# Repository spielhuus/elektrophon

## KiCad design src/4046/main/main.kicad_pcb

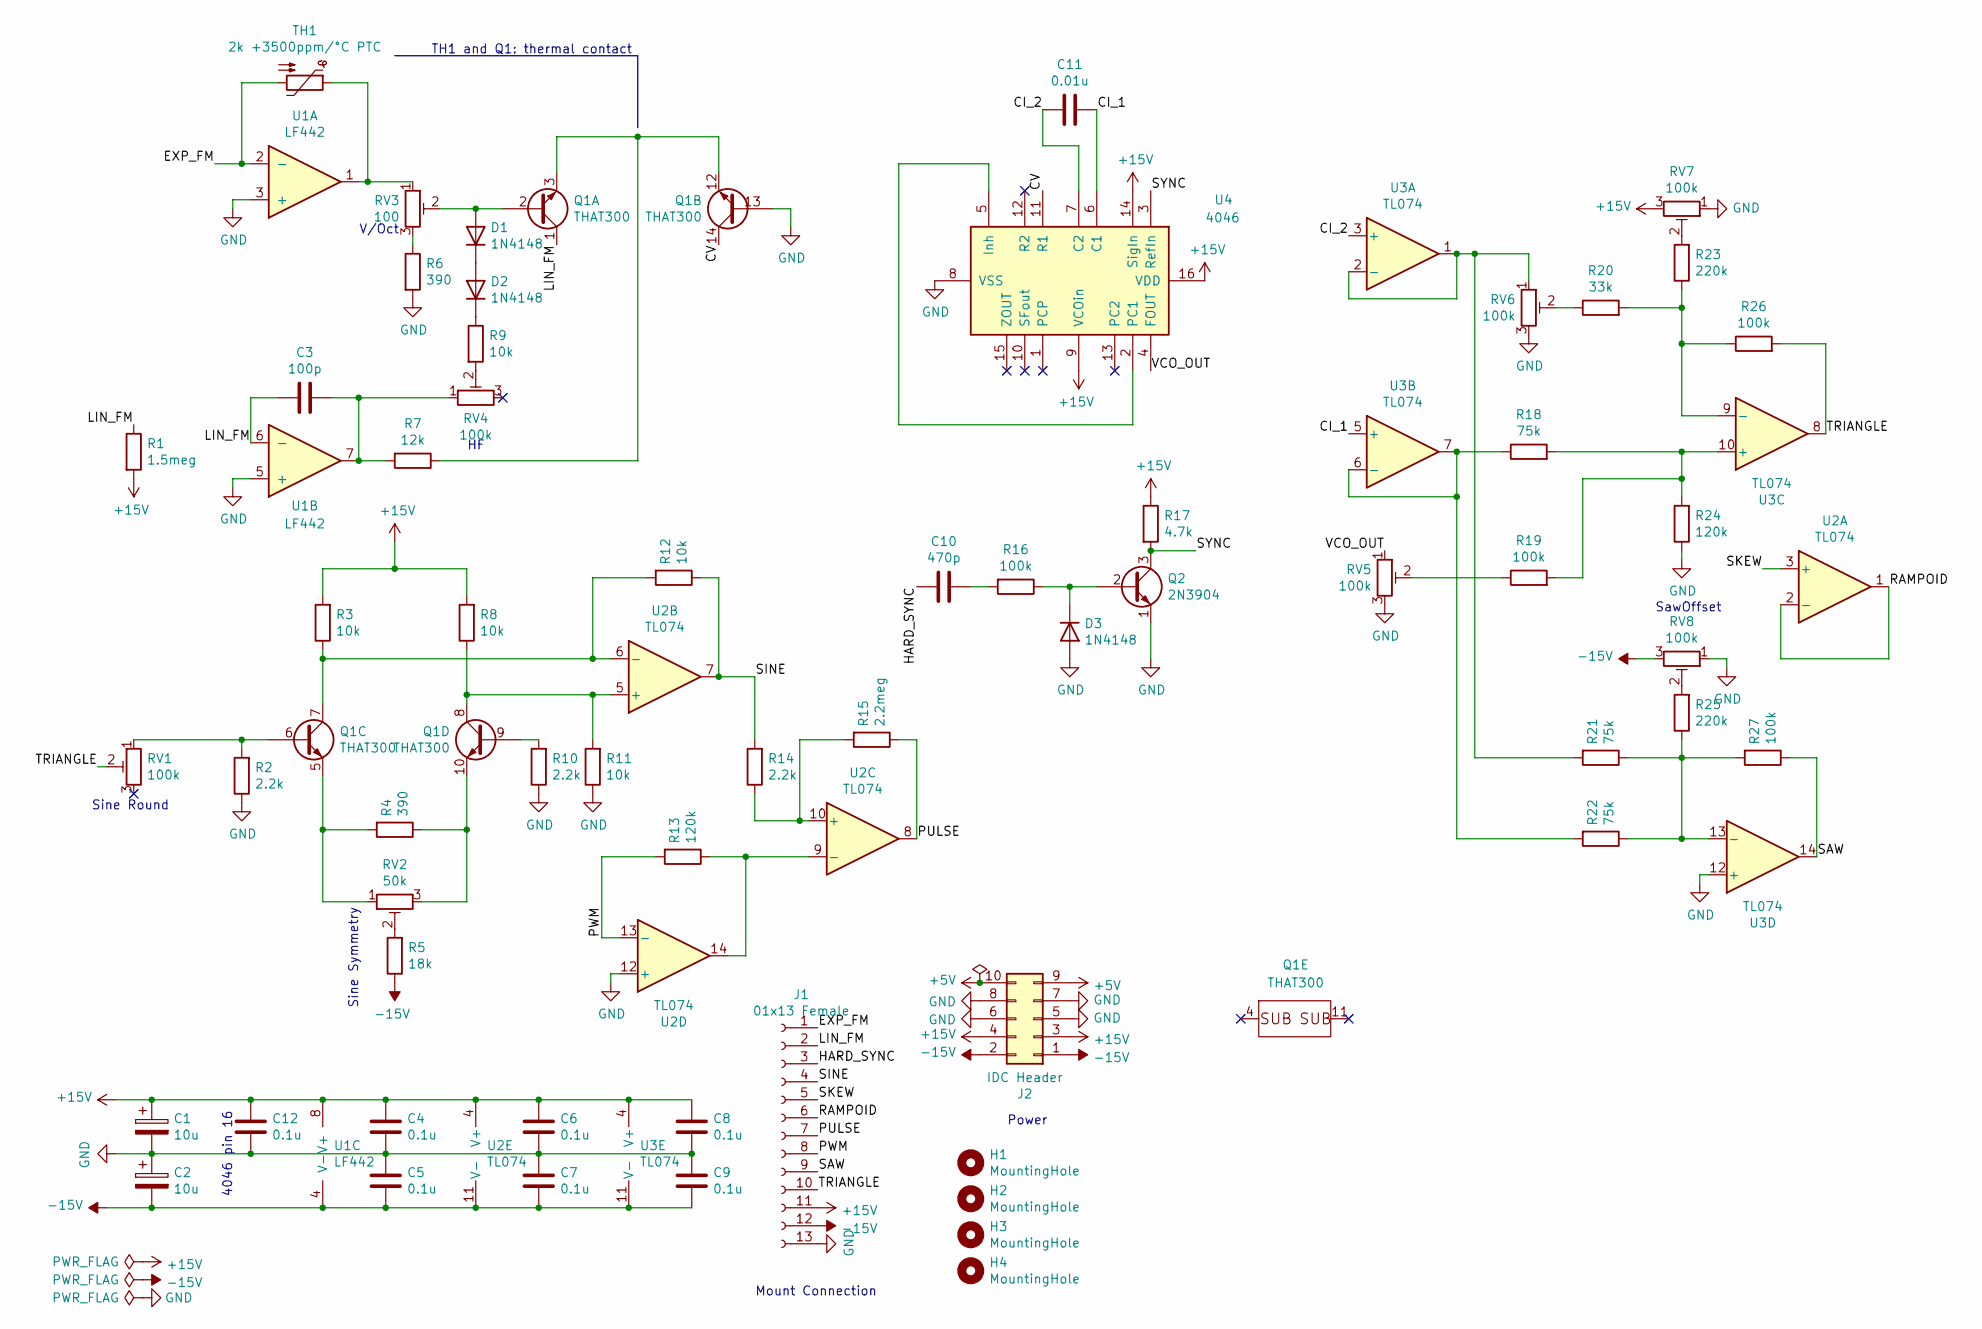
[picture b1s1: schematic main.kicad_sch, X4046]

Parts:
C1, C2: 10u; CP_Radial_D5.0mm_P2.50mm
C3: 100p; C_Disc_D3.4mm_W2.1mm_P2.50mm
C4, C5, C6, C7, C8, C9, C12: 0.1u; C_Disc_D3.4mm_W2.1mm_P2.50mm
C10: 470p; C_Disc_D3.4mm_W2.1mm_P2.50mm
C11: 0.01u; C_Rect_L4.6mm_W3.0mm_P2.50mm_MKS02_FKP02
D1, D2, D3: 1N4148; D_DO-35_SOD27_P7.62mm_Horizontal
H1, H2, H3, H4: MountingHole; MountingHole_2.2mm_M2
J1: 01x13 Female; PinSocket_1x13_P2.54mm_Vertical
J2: IDC Header; IDC-Header_2x05_P2.54mm_Vertical
Q1: THAT300; DIP-14_W7.62mm_Socket
Q2: 2N3904; TO-92_Inline_Wide
R1: 1.5meg; R_Axial_DIN0207_L6.3mm_D2.5mm_P10.16mm_Horizontal
R2, R10, R14: 2.2k; R_Axial_DIN0207_L6.3mm_D2.5mm_P10.16mm_Horizontal
R3, R8, R9, R11: 10k; R_Axial_DIN0207_L6.3mm_D2.5mm_P10.16mm_Horizontal
R4, R6: 390; R_Axial_DIN0207_L6.3mm_D2.5mm_P10.16mm_Horizontal
R5: 18k; R_Axial_DIN0207_L6.3mm_D2.5mm_P10.16mm_Horizontal
R7: 12k; R_Axial_DIN0207_L6.3mm_D2.5mm_P10.16mm_Horizontal
R12: 10k; R_Axial_DIN0207_L6.3mm_D2.5mm_P2.54mm_Vertical
R13: 120k; R_Axial_DIN0207_L6.3mm_D2.5mm_P2.54mm_Vertical
R15: 2.2meg; R_Axial_DIN0207_L6.3mm_D2.5mm_P2.54mm_Vertical
R16, R19: 100k; R_Axial_DIN0207_L6.3mm_D2.5mm_P10.16mm_Horizontal
R17: 4.7k; R_Axial_DIN0207_L6.3mm_D2.5mm_P10.16mm_Horizontal
R18, R21, R22: 75k; R_Axial_DIN0207_L6.3mm_D2.5mm_P10.16mm_Horizontal
R20: 33k; R_Axial_DIN0207_L6.3mm_D2.5mm_P10.16mm_Horizontal
R23, R25: 220k; R_Axial_DIN0207_L6.3mm_D2.5mm_P10.16mm_Horizontal
R24: 120k; R_Axial_DIN0207_L6.3mm_D2.5mm_P10.16mm_Horizontal
R26, R27: 100k; R_Axial_DIN0207_L6.3mm_D2.5mm_P2.54mm_Vertical
RV1, RV4, RV5, RV6, RV7, RV8: 100k; Potentiometer_Bourns_3296Z_Horizontal
RV2: 50k; Potentiometer_Bourns_3296Z_Horizontal
RV3: 100; Potentiometer_Bourns_3296Z_Horizontal
TH1: 2k +3500ppm/°C PTC; R_Axial_DIN0204_L3.6mm_D1.6mm_P2.54mm_Vertical
U1: LF442; DIP-8_W7.62mm_Socket
U2, U3: TL074; DIP-14_W7.62mm_Socket
U4: 4046; DIP-16_W7.62mm_Socket

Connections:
+5V: J2.9, J2.10
+15V: C1.1, C4.1, C6.1, C8.1, C12.1, J1.11, J2.3, J2.4, R1.2, R3.2, R8.2, R17.1, RV7.3, U1.8 (V+), U2.4 (V+), U3.4 (V+), U4.9 (VCOin), U4.14 (SigIn), U4.16 (VDD)
-15V: C2.2, C5.2, C7.2, C9.2, J1.12, J2.1, J2.2, R5.1, RV8.3, U1.4 (V-), U2.11 (V-), U3.11 (V-)
/CI_1: C11.2, U3.5 (+), U4.6 (C1)
/CI_2: C11.1, U3.3 (+), U4.7 (C2)
/CV: Q1.14 (C), U4.11 (R1)
/EXP_FM: J1.1, TH1.2, U1.2 (-)
/HARD_SYNC: C10.2, J1.3
/LIN_FM: C3.2, J1.2, Q1.1 (C), R1.1, U1.6 (-)
/PULSE: J1.7, R15.1, U2.8
/PWM: J1.8, R13.2, U2.13 (-)
/RAMPOID: J1.6, U2.1, U2.2 (-)
/SAW: J1.9, R27.1, U3.14
/SINE: J1.4, R12.1, R14.2, U2.7
/SKEW: J1.5, U2.3 (+)
/SYNC: Q2.3 (C), R17.2, U4.3 (RefIn)
/TRIANGLE: J1.10, R26.2, RV1.2, U3.8
/VCO_OUT: RV5.1, U4.4 (FOUT)
GND: C1.2, C2.1, C4.2, C5.1, C6.2, C7.1, C8.2, C9.1, C12.2, D3.2 (A), J1.13, J2.5, J2.6, J2.7, J2.8, Q1.13 (B), Q2.1 (E), R2.1, R6.2, R10.1, R11.1, R24.1, RV5.3, RV6.3, RV7.1, RV8.1, U1.3 (+), U1.5 (+), U2.12 (+), U3.12 (+), U4.8 (VSS)
unnamed: C3.1, R7.2, RV4.1, U1.7
unnamed: C10.1, R16.2
unnamed: D1.2 (A), Q1.2 (B), RV3.2
unnamed: D1.1 (K), D2.2 (A)
unnamed: D2.1 (K), R9.1
unnamed: D3.1 (K), Q2.2 (B), R16.1
unnamed: Q1.3 (E), Q1.12 (E), R7.1
unnamed: Q1.6 (B), R2.2, RV1.1
unnamed: Q1.7 (C), R3.1, R12.2, U2.6 (-)
unnamed: Q1.5 (E), R4.2, RV2.1
unnamed: Q1.9 (B), R10.2
unnamed: Q1.10 (E), R4.1, RV2.3
unnamed: R5.2, RV2.2
unnamed: R6.1, RV3.3
unnamed: R9.2, RV4.2
unnamed: R19.1, RV5.2
unnamed: R20.1, RV6.2
unnamed: R23.2, RV7.2
unnamed: R25.2, RV8.2
unnamed: RV3.1, TH1.1, U1.1
unnamed: Q1.8, R8.1, R11.2, U2.5 (+)
unnamed: R14.1, R15.2, U2.10 (+)
unnamed: R13.1, U2.9 (-), U2.14
unnamed: R21.2, RV6.1, U3.1, U3.2 (-)
unnamed: R18.1, R22.2, U3.6 (-), U3.7
unnamed: R18.2, R19.2, R24.2, U3.10 (+)
unnamed: R20.2, R23.1, R26.1, U3.9 (-)
unnamed: R21.1, R22.1, R25.1, R27.2, U3.13 (-)
unnamed: U4.2 (PC1), U4.5 (Inh)

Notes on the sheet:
Power
4046 pin 16
TH1 and Q1: thermal contact
SawOffset
Mount Connection
Sine Round
V/Oct
Sine Symmetry

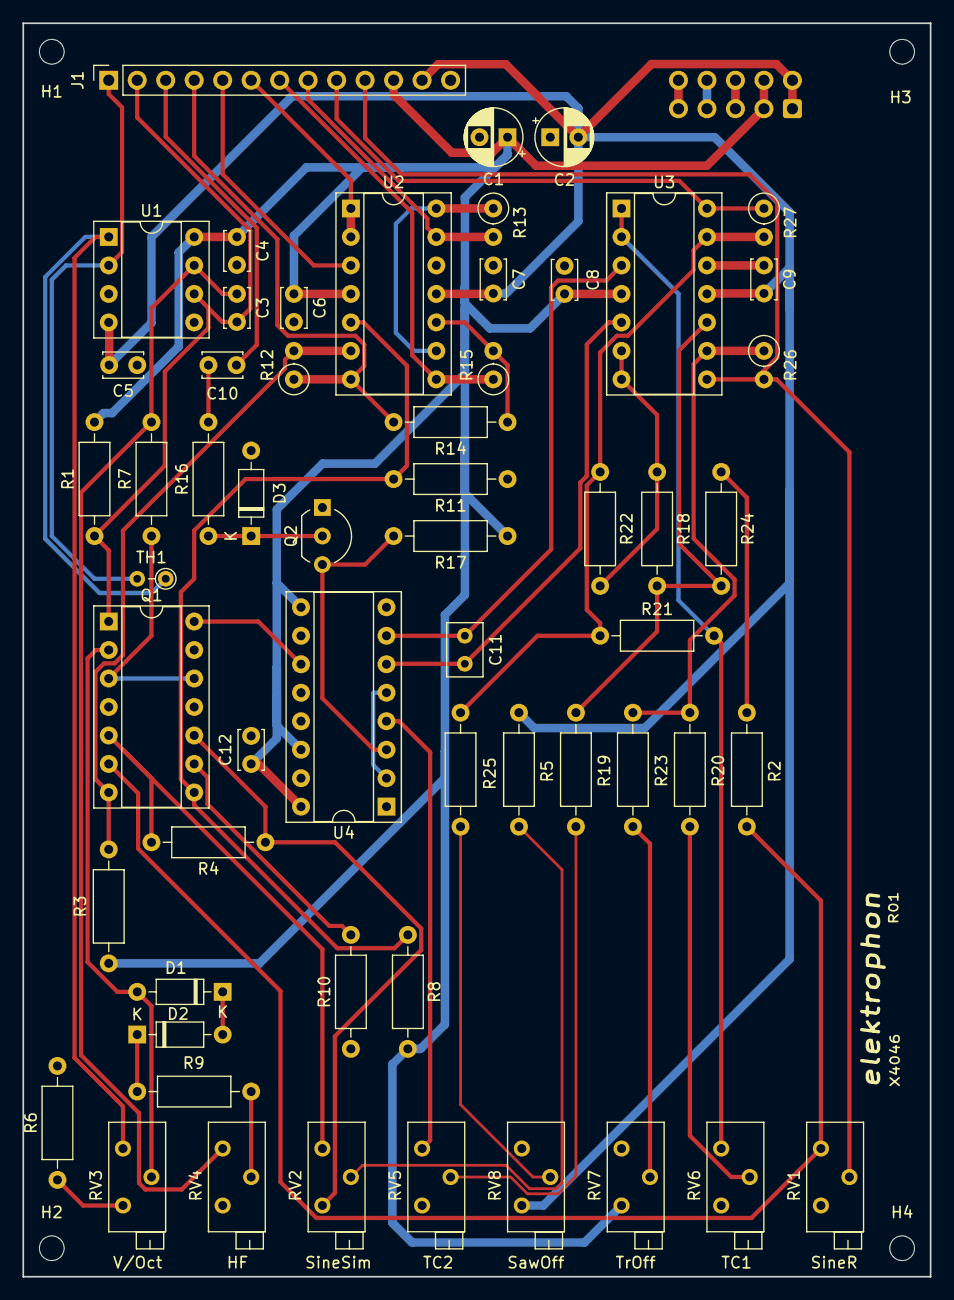
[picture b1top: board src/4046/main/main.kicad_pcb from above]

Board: 2 copper layers, 80.9 x 111.8 mm, 63 parts (1 on the bottom side), 48 nets.

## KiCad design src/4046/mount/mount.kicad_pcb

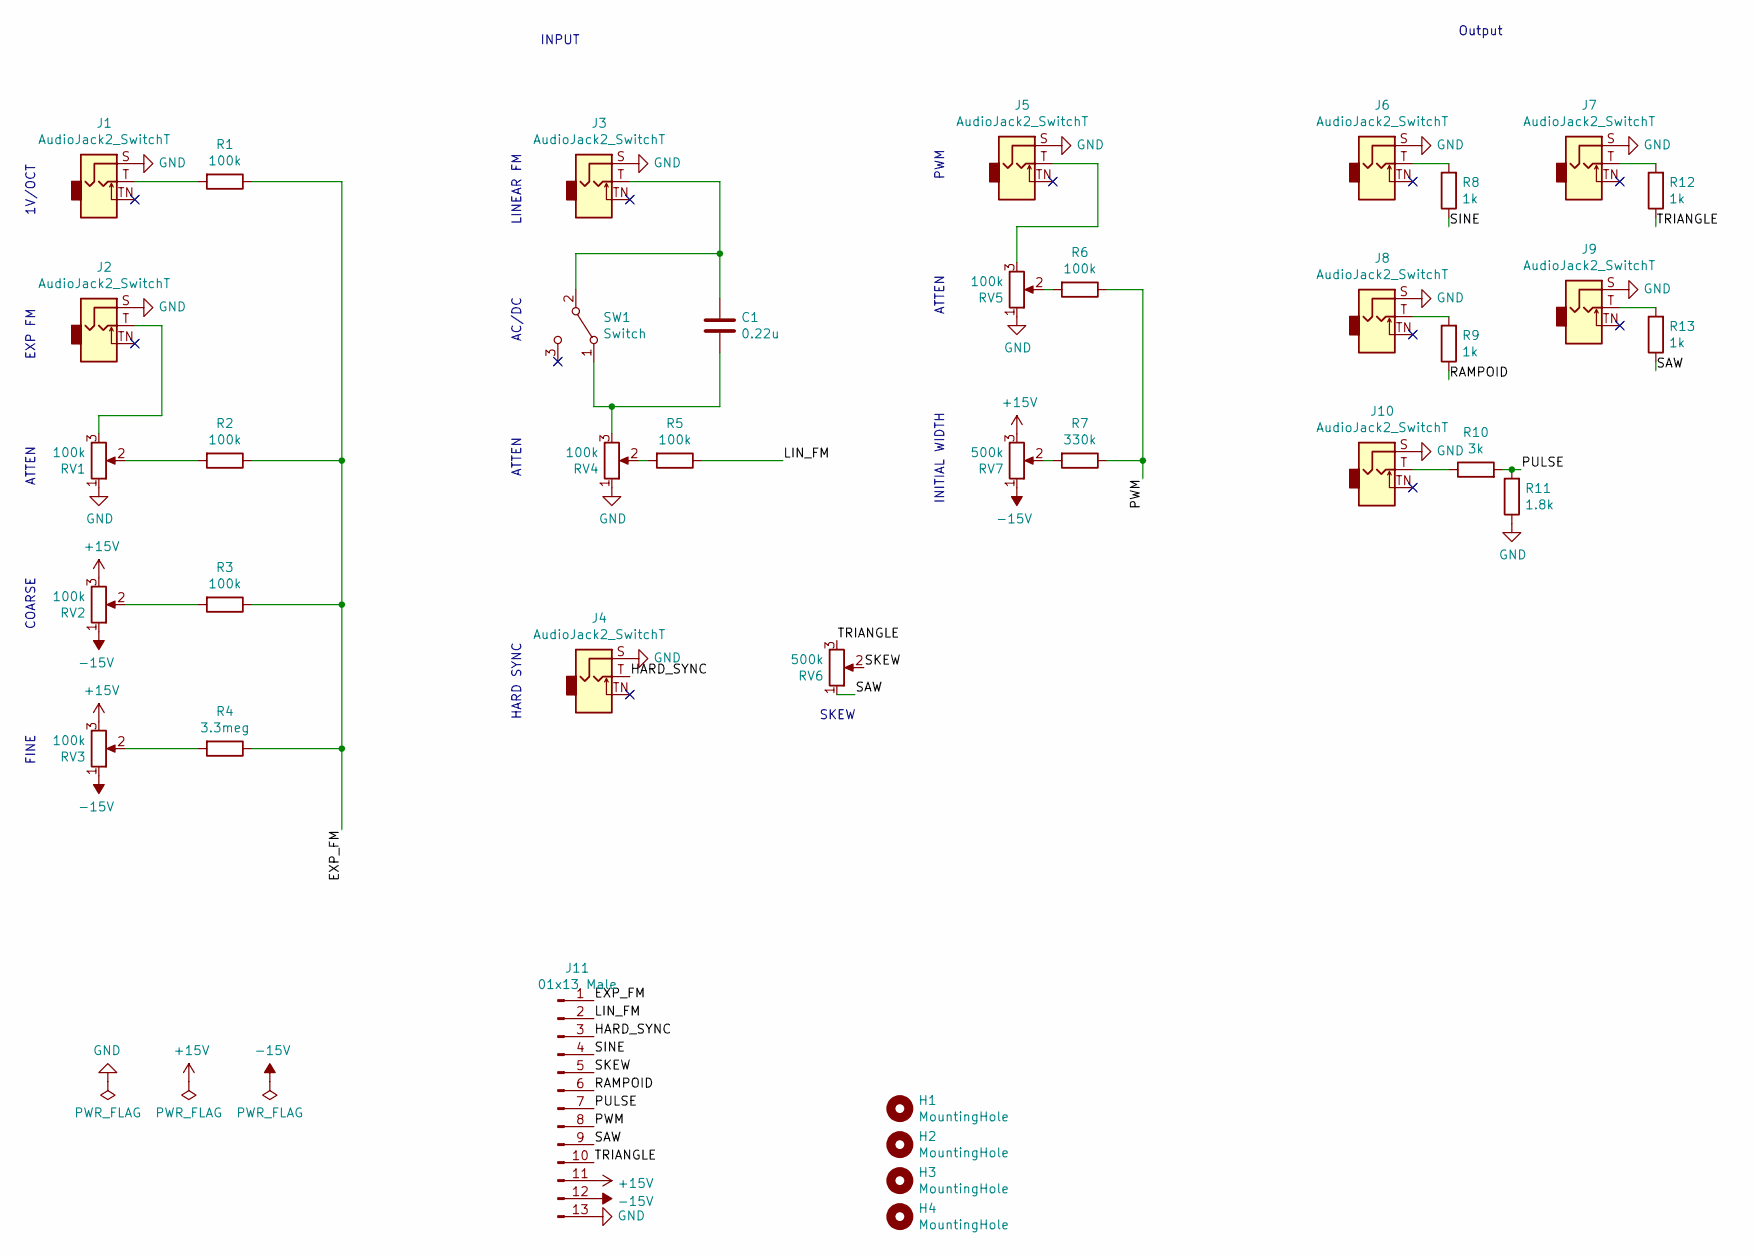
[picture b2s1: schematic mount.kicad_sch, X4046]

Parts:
C1: 0.22u; C_Rect_L4.6mm_W3.0mm_P2.50mm_MKS02_FKP02
H1, H2, H3, H4: MountingHole; MountingHole_2.2mm_M2
J1, J2, J3, J4, J5, J6, J7, J8, J9, J10: AudioJack2_SwitchT; Jack_3.5mm_WQP-PJ398SM_Vertical
J11: 01x13 Male; PinHeader_1x13_P2.54mm_Vertical
R1, R2, R3, R5, R6: 100k; R_Axial_DIN0207_L6.3mm_D2.5mm_P10.16mm_Horizontal
R4: 3.3meg; R_Axial_DIN0207_L6.3mm_D2.5mm_P10.16mm_Horizontal
R7: 330k; R_Axial_DIN0207_L6.3mm_D2.5mm_P10.16mm_Horizontal
R8, R9: 1k; R_Axial_DIN0207_L6.3mm_D2.5mm_P10.16mm_Horizontal
R10: 3k; R_Axial_DIN0207_L6.3mm_D2.5mm_P7.62mm_Horizontal
R11: 1.8k; R_Axial_DIN0207_L6.3mm_D2.5mm_P7.62mm_Horizontal
R12, R13: 1k; R_Axial_DIN0207_L6.3mm_D2.5mm_P7.62mm_Horizontal
RV1, RV2, RV3, RV4, RV5: 100k; Potentiometer_Alpha_RD901F-40-00D_Single_Vertical
RV6, RV7: 500k; Potentiometer_Alpha_RD901F-40-00D_Single_Vertical
SW1: Switch; SPDT_KIT

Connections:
+15V: J11.11, RV2.3, RV3.3, RV7.3
-15V: J11.12, RV2.1, RV3.1, RV7.1
/EXP_FM: J11.1, R1.1, R2.1, R3.1, R4.1
/HARD_SYNC: J4.T, J11.3
/LIN_FM: J11.2, R5.1
/PULSE: J11.7, R10.2, R11.2
/PWM: J11.8, R6.1, R7.1
/RAMPOID: J11.6, R9.1
/SAW: J11.9, R13.1, RV6.1
/SINE: J11.4, R8.1
/SKEW: J11.5, RV6.2
/TRIANGLE: J11.10, R12.1, RV6.3
GND: J1.S, J2.S, J3.S, J4.S, J5.S, J6.S, J7.S, J8.S, J9.S, J10.S, J11.13, R11.1, RV1.1, RV4.1, RV5.1
unnamed: J1.T, R1.2
unnamed: J2.T, RV1.3
unnamed: J5.T, RV5.3
unnamed: J6.T, R8.2
unnamed: J7.T, R12.2
unnamed: J8.T, R9.2
unnamed: J9.T, R13.2
unnamed: J10.T, R10.1
unnamed: R2.2, RV1.2
unnamed: R3.2, RV2.2
unnamed: R4.2, RV3.2
unnamed: R5.2, RV4.2
unnamed: R6.2, RV5.2
unnamed: R7.2, RV7.2
unnamed: C1.2, RV4.3, SW1.1 (A)
unnamed: C1.1, J3.T, SW1.2 (B)

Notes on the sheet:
ATTEN
INITIAL WIDTH
FINE
LINEAR FM
INPUT
HARD SYNC
AC/DC
1V/OCT
Output
COARSE
EXP FM
PWM
SKEW

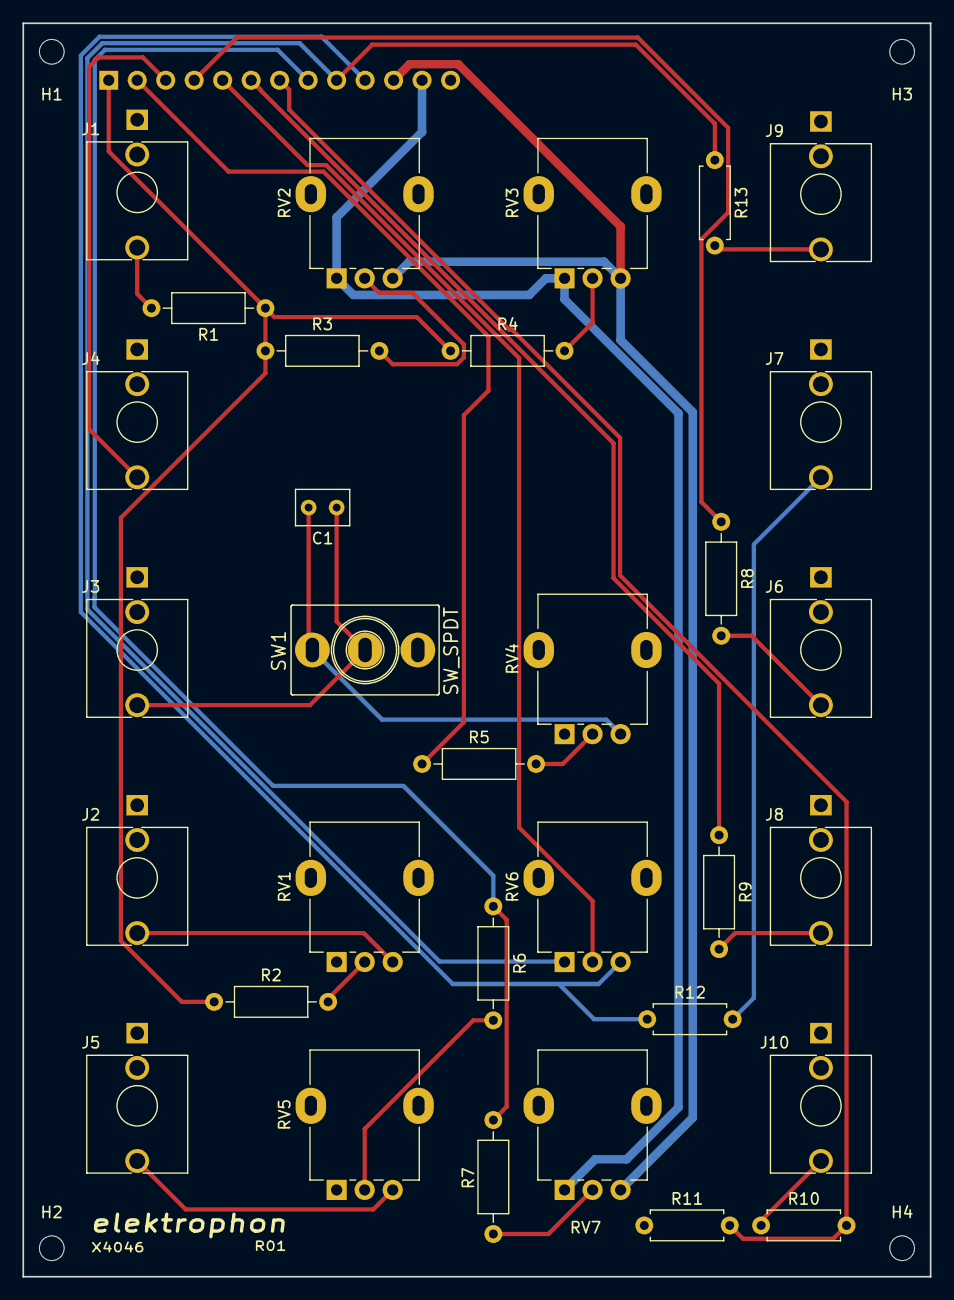
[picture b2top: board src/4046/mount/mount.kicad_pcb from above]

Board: 2 copper layers, 80.9 x 111.8 mm, 37 parts (1 on the bottom side), 29 nets.

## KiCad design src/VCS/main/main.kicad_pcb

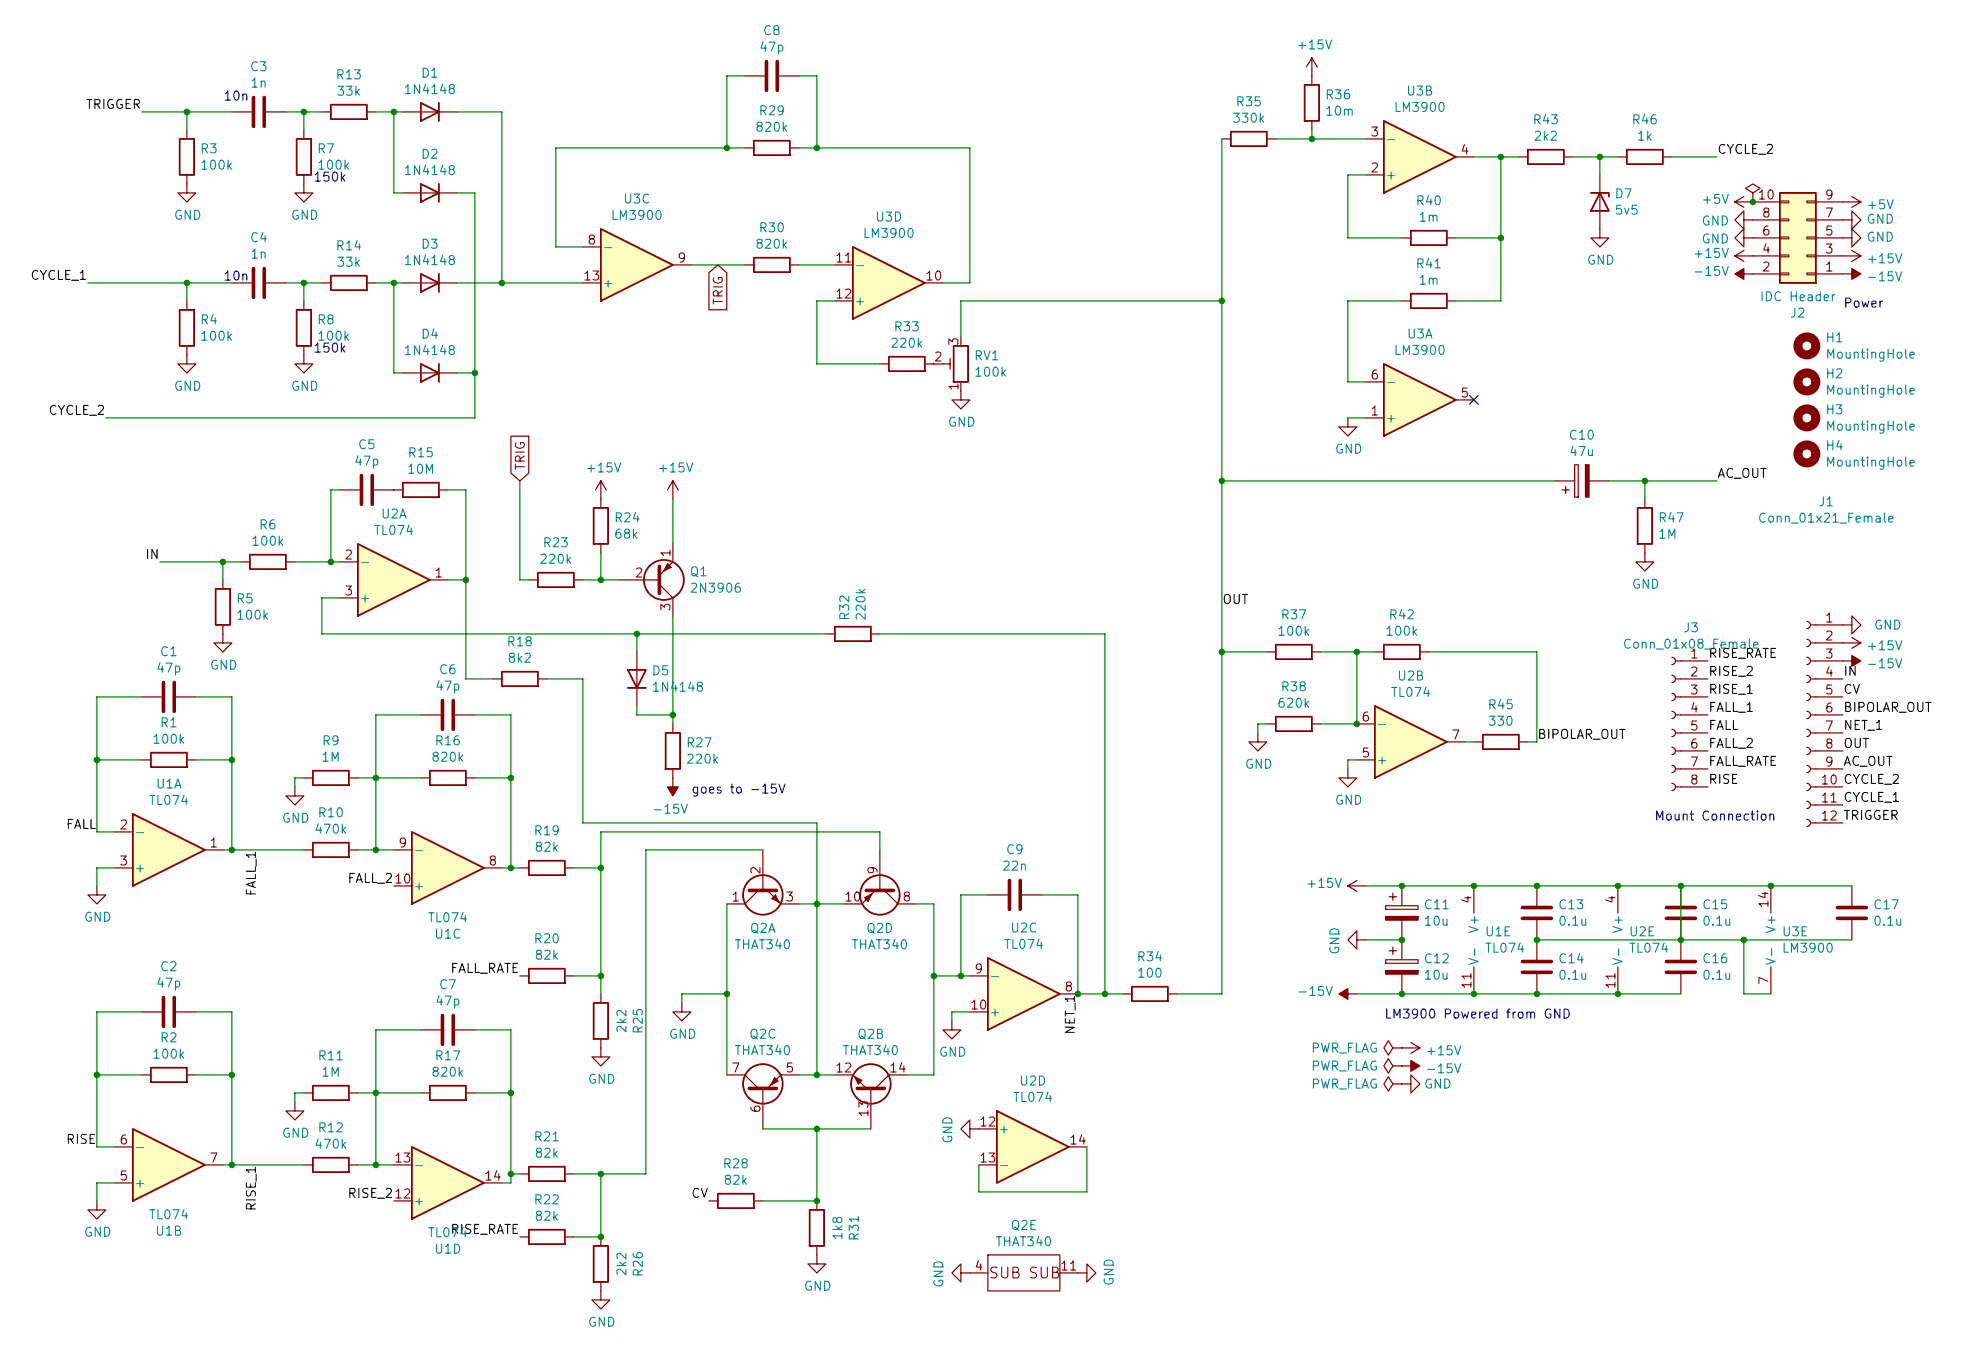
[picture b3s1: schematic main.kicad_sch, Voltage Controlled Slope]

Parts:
C1, C2, C5, C6, C7: 47p; C_Disc_D3.4mm_W2.1mm_P2.50mm
C3, C4: 1n; C_Disc_D3.4mm_W2.1mm_P2.50mm
C8: 47p; C_Disc_D5.0mm_W2.5mm_P2.50mm
C9: 22n; C_Disc_D3.4mm_W2.1mm_P2.50mm
C10: 47u; CP_Radial_D5.0mm_P2.50mm
C11, C12: 10u; CP_Radial_D5.0mm_P2.50mm
C13, C14, C15, C16, C17: 0.1u; C_Disc_D3.4mm_W2.1mm_P2.50mm
D1, D2, D3, D4, D5: 1N4148; D_DO-35_SOD27_P7.62mm_Horizontal
D7: 5v5; D_DO-35_SOD27_P10.16mm_Horizontal
H1, H2, H3, H4: MountingHole; MountingHole_2.2mm_M2
J1: Conn_01x21_Female; PinSocket_1x21_P2.54mm_Vertical
J2: IDC Header; IDC-Header_2x05_P2.54mm_Vertical
J3: Conn_01x08_Female; PinHeader_1x08_P2.54mm_Vertical
Q1: 2N3906; TO-92_Inline
Q2: THAT340; DIP-14_W7.62mm_Socket
R1, R2: 100k; R_Axial_DIN0207_L6.3mm_D2.5mm_P2.54mm_Vertical
R3, R4, R5, R6, R7, R8, R37, R42: 100k; R_Axial_DIN0207_L6.3mm_D2.5mm_P10.16mm_Horizontal
R9, R11, R47: 1M; R_Axial_DIN0207_L6.3mm_D2.5mm_P10.16mm_Horizontal
R10, R12: 470k; R_Axial_DIN0207_L6.3mm_D2.5mm_P10.16mm_Horizontal
R13, R14: 33k; R_Axial_DIN0207_L6.3mm_D2.5mm_P10.16mm_Horizontal
R15: 10M; R_Axial_DIN0207_L6.3mm_D2.5mm_P10.16mm_Horizontal
R16: 820k; R_Axial_DIN0207_L6.3mm_D2.5mm_P2.54mm_Vertical
R17, R30: 820k; R_Axial_DIN0207_L6.3mm_D2.5mm_P10.16mm_Horizontal
R18: 8k2; R_Axial_DIN0207_L6.3mm_D2.5mm_P10.16mm_Horizontal
R19, R20, R21, R22, R28: 82k; R_Axial_DIN0207_L6.3mm_D2.5mm_P10.16mm_Horizontal
R23, R27, R32, R33: 220k; R_Axial_DIN0207_L6.3mm_D2.5mm_P10.16mm_Horizontal
R24: 68k; R_Axial_DIN0207_L6.3mm_D2.5mm_P10.16mm_Horizontal
R25, R26, R43: 2k2; R_Axial_DIN0207_L6.3mm_D2.5mm_P10.16mm_Horizontal
R29: 820k; R_Axial_DIN0207_L6.3mm_D2.5mm_P5.08mm_Vertical
R31: 1k8; R_Axial_DIN0207_L6.3mm_D2.5mm_P10.16mm_Horizontal
R34: 100; R_Axial_DIN0207_L6.3mm_D2.5mm_P10.16mm_Horizontal
R35: 330k; R_Axial_DIN0207_L6.3mm_D2.5mm_P10.16mm_Horizontal
R36: 10m; R_Axial_DIN0207_L6.3mm_D2.5mm_P10.16mm_Horizontal
R38: 620k; R_Axial_DIN0207_L6.3mm_D2.5mm_P10.16mm_Horizontal
R40: 1m; R_Axial_DIN0207_L6.3mm_D2.5mm_P7.62mm_Horizontal
R41: 1m; R_Axial_DIN0207_L6.3mm_D2.5mm_P2.54mm_Vertical
R45: 330; R_Axial_DIN0207_L6.3mm_D2.5mm_P10.16mm_Horizontal
R46: 1k; R_Axial_DIN0207_L6.3mm_D2.5mm_P10.16mm_Horizontal
RV1: 100k; Potentiometer_Bourns_3296Z_Horizontal
U1, U2: TL074; DIP-14_W7.62mm_Socket
U3: LM3900; DIP-14_W7.62mm_Socket

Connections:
+5V: J2.9, J2.10
+15V: C11.1, C13.1, C13.2, C14.1, C15.1, C15.2, C16.1, C17.1, C17.2, J1.2, J2.3, J2.4, Q1.1 (E), R24.1, R36.1, U1.4 (V+), U2.4 (V+), U3.7 (V-), U3.14 (V+); also elsewhere on the board
-15V: C12.2, C14.2, C16.2, J1.3, J2.1, J2.2, R27.2, U1.11 (V-), U2.11 (V-); also elsewhere on the board
/AC_OUT: C10.2, J1.9, R47.1
/BIPOLAR_OUT: J1.6, R42.2, R45.2
/CV: J1.5, R28.1
/CYCLE_1: C4.2, J1.11, R4.2
/CYCLE_2: D2.1 (K), D4.1 (K), J1.10, R46.1
/FALL: C1.1, J3.5, R1.1, U1.2 (-)
/FALL_1: C1.2, J3.4, R1.2, R10.1, U1.1
/FALL_2: J3.6, U1.10 (+)
/FALL_RATE: J3.7, R20.1
/IN: J1.4, R5.2, R6.1
/NET_1: C9.2, J1.7, R32.2, R34.1, U2.8
/OUT: C10.1, J1.8, R34.2, R35.2, R37.1, RV1.3
/RISE: C2.1, J3.8, R2.1, U1.6 (-)
/RISE_1: C2.2, J3.3, R2.2, R12.1, U1.7
/RISE_2: J3.2, U1.12 (+)
/RISE_RATE: J3.1, R22.1
/TRIGGER: C3.2, J1.12, R3.2
GND: C11.2, C12.1, D7.2 (A), J1.1, J2.5, J2.6, J2.7, J2.8, Q2.1 (C), Q2.4 (B), Q2.7 (E), Q2.11 (E), R3.1, R4.1, R5.1, R7.1, R8.1, R9.1, R11.1, R25.2, R26.2, R31.2, R38.1, R47.2, RV1.1, U1.3 (+), U1.5 (+), U2.5 (+), U2.10 (+), U2.12 (+), U3.1 (+)
unnamed: C3.1, R7.2, R13.1
unnamed: C4.1, R8.2, R14.1
unnamed: C5.1, R15.1
unnamed: C5.2, R6.2, U2.2 (-)
unnamed: C6.1, R9.2, R10.2, R16.1, U1.9 (-)
unnamed: C6.2, R16.2, R19.1, U1.8
unnamed: C7.1, R11.2, R12.2, R17.1, U1.13 (-)
unnamed: C7.2, R17.2, R21.1, U1.14
unnamed: C8.1, R29.1, U3.8 (-)
unnamed: C8.2, R29.2, U3.10
unnamed: C9.1, Q2.8 (E), Q2.14 (C), U2.9 (-)
unnamed: D1.1 (K), D3.1 (K), U3.13 (+)
unnamed: D1.2 (A), D2.2 (A), R13.2
unnamed: D3.2 (A), D4.2 (A), R14.2
unnamed: D5.1 (K), Q1.3 (C), R27.1
unnamed: D5.2 (A), R32.1, U2.3 (+)
unnamed: D7.1 (K), R43.1, R46.2
unnamed: Q1.2 (B), R23.2, R24.2
unnamed: Q2.2 (B), R21.2, R22.2, R26.1
unnamed: Q2.9 (B), R19.2, R20.2, R25.1
unnamed: Q2.3 (E), Q2.5 (C), Q2.10, Q2.12 (E), R18.2
unnamed: Q2.6 (B), Q2.13 (B), R28.2, R31.1
unnamed: R15.2, R18.1, U2.1
unnamed: R30.2, U3.11 (-)
unnamed: R33.1, U3.12 (+)
unnamed: R33.2, RV1.2
unnamed: R35.1, R36.2, U3.3 (-)
unnamed: R37.2, R38.2, R42.1, U2.6 (-)
unnamed: R40.1, R41.1, R43.2, U3.4
unnamed: R40.2, U3.2 (+)
unnamed: R41.2, U3.6 (-)
unnamed: R45.1, U2.7
unnamed: U2.13 (-), U2.14
TRIG: R23.1, R30.1, U3.9

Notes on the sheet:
150k
LM3900 Powered from GND
10n
Mount Connection
goes to -15V
Power

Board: 2 copper layers, 81 parts (1 on the bottom side), 55 nets, no tracks yet.

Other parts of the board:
C18: 0.1u; C_Disc_D3.4mm_W2.1mm_P2.50mm

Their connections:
+15V: C18.1; also elsewhere on the board
-15V: C18.2; also elsewhere on the board

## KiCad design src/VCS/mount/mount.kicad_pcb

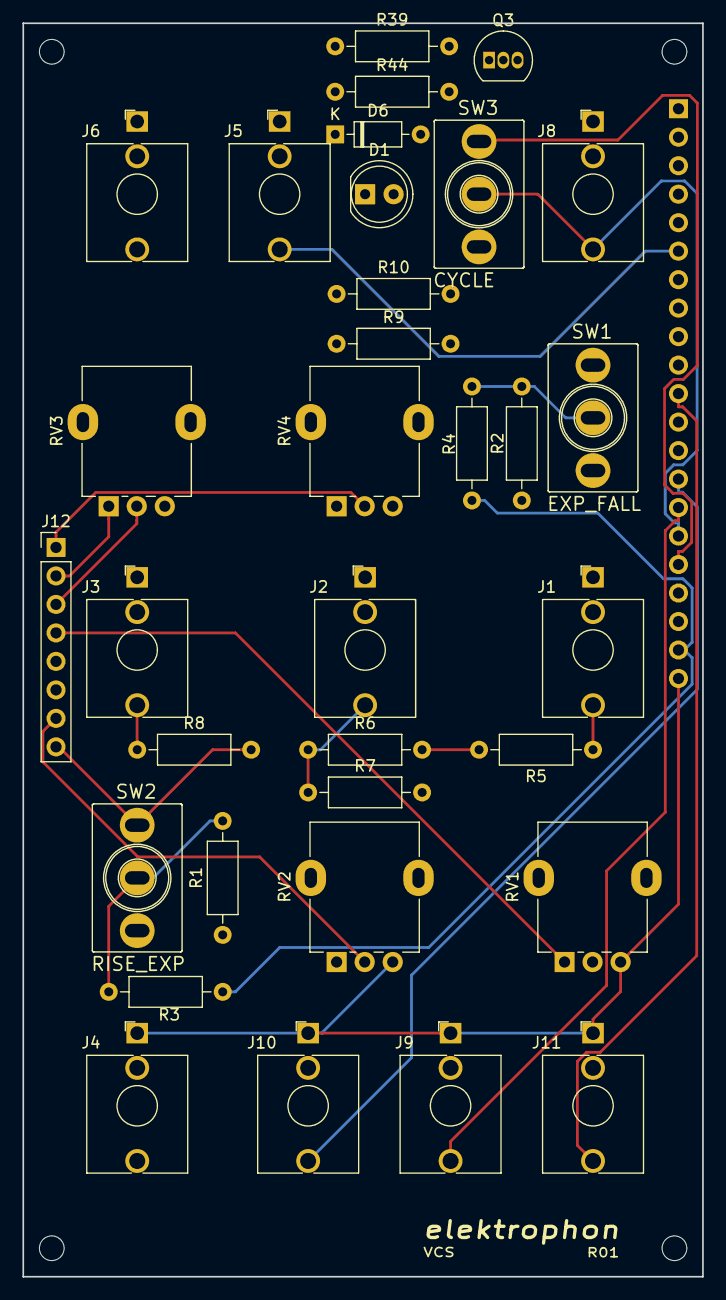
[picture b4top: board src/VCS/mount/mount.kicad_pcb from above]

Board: 2 copper layers, 60.6 x 111.8 mm, 38 parts (1 on the bottom side), 28 nets.

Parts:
D1: LED; LED_D5.0mm_Clear
D6: 1N4148; D_DO-35_SOD27_P7.62mm_Horizontal
H1, H2, H3, H4: MountingHole; MountingHole_2.2mm_M2
J1: FALL CV; Jack_3.5mm_QingPu_WQP-PJ398SM_Vertical_CircularHoles
J2: BOTH CV; Jack_3.5mm_QingPu_WQP-PJ398SM_Vertical_CircularHoles
J3: RISE CV; Jack_3.5mm_QingPu_WQP-PJ398SM_Vertical_CircularHoles
J4: CV (1V/OCT); Jack_3.5mm_QingPu_WQP-PJ398SM_Vertical_CircularHoles
J5: IN; Jack_3.5mm_QingPu_WQP-PJ398SM_Vertical_CircularHoles
J6: TRIGGER; Jack_3.5mm_QingPu_WQP-PJ398SM_Vertical_CircularHoles
J7: Conn_01x21_Male; PinHeader_1x21_P2.54mm_Vertical
J8: END; Jack_3.5mm_QingPu_WQP-PJ398SM_Vertical_CircularHoles
J9: AC OUT; Jack_3.5mm_QingPu_WQP-PJ398SM_Vertical_CircularHoles
J10: OUT; Jack_3.5mm_QingPu_WQP-PJ398SM_Vertical_CircularHoles
J11: BIPOLAR OUT; Jack_3.5mm_QingPu_WQP-PJ398SM_Vertical_CircularHoles
J12: Conn_01x08_Female; PinHeader_1x08_P2.54mm_Vertical
Q3: 2N3904; TO-92_Inline
R1, R2: 330k; R_Axial_DIN0207_L6.3mm_D2.5mm_P10.16mm_Horizontal
R3, R4, R9, R10: 1M; R_Axial_DIN0207_L6.3mm_D2.5mm_P10.16mm_Horizontal
R5, R6, R7, R8: 100k; R_Axial_DIN0207_L6.3mm_D2.5mm_P10.16mm_Horizontal
R39: 150k; R_Axial_DIN0207_L6.3mm_D2.5mm_P10.16mm_Horizontal
R44: 1k; R_Axial_DIN0207_L6.3mm_D2.5mm_P10.16mm_Horizontal
RV1, RV3: 50k; Potentiometer_Alpha_RD901F-40-00D_Single_Vertical
RV2, RV4: 100k; Potentiometer_Alpha_RD901F-40-00D_Single_Vertical
SW1: EXP_FALL; SPDT_KIT
SW2: RISE_EXP; SPDT_KIT
SW3: CYCLE; SPDT_KIT

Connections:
+15V: D1.2, J7.2, RV2.1, RV4.1
-15V: J7.3, R3.2, R4.2
/AC_OUT: J7.18, J9.T
/BIPOLAR_OUT: J7.14, J11.T
/CV: J4.T, J7.13
/CYCLE_1: J7.20, SW3.1
/CYCLE_2: J7.19, J8.T, SW3.2
/FALL: J12.5, R5.2, R6.2, SW1.1
/FALL_1: J12.4, RV1.1
/FALL_2: J12.6, R9.2, RV1.2
/FALL_RATE: J12.7, RV2.2
/IN: J5.T, J7.9
/NET_1: J7.15, R1.1, R2.1
/OUT: J7.17, J10.T, R39.1
/RISE: J12.8, R7.2, R8.2, SW2.1
/RISE_1: J12.2, RV3.1
/RISE_2: J12.3, R10.2, RV3.2
/RISE_RATE: J12.1, RV4.2
/TRIGGER: J6.T, J7.21
GND: D6.2, J1.S, J2.S, J3.S, J4.S, J5.S, J6.S, J7.1, J8.S, J9.S, J10.S, J11.S, Q3.1, R9.1, R10.1, RV1.3, RV2.3, RV3.3, RV4.3
unnamed: D1.1, R44.2
unnamed: D6.1, Q3.2, R39.2
unnamed: J1.T, R5.1
unnamed: J2.T, R6.1, R7.1
unnamed: J3.T, R8.1
unnamed: Q3.3, R44.1
unnamed: R1.2, R3.1, SW2.2
unnamed: R2.2, R4.1, SW1.2

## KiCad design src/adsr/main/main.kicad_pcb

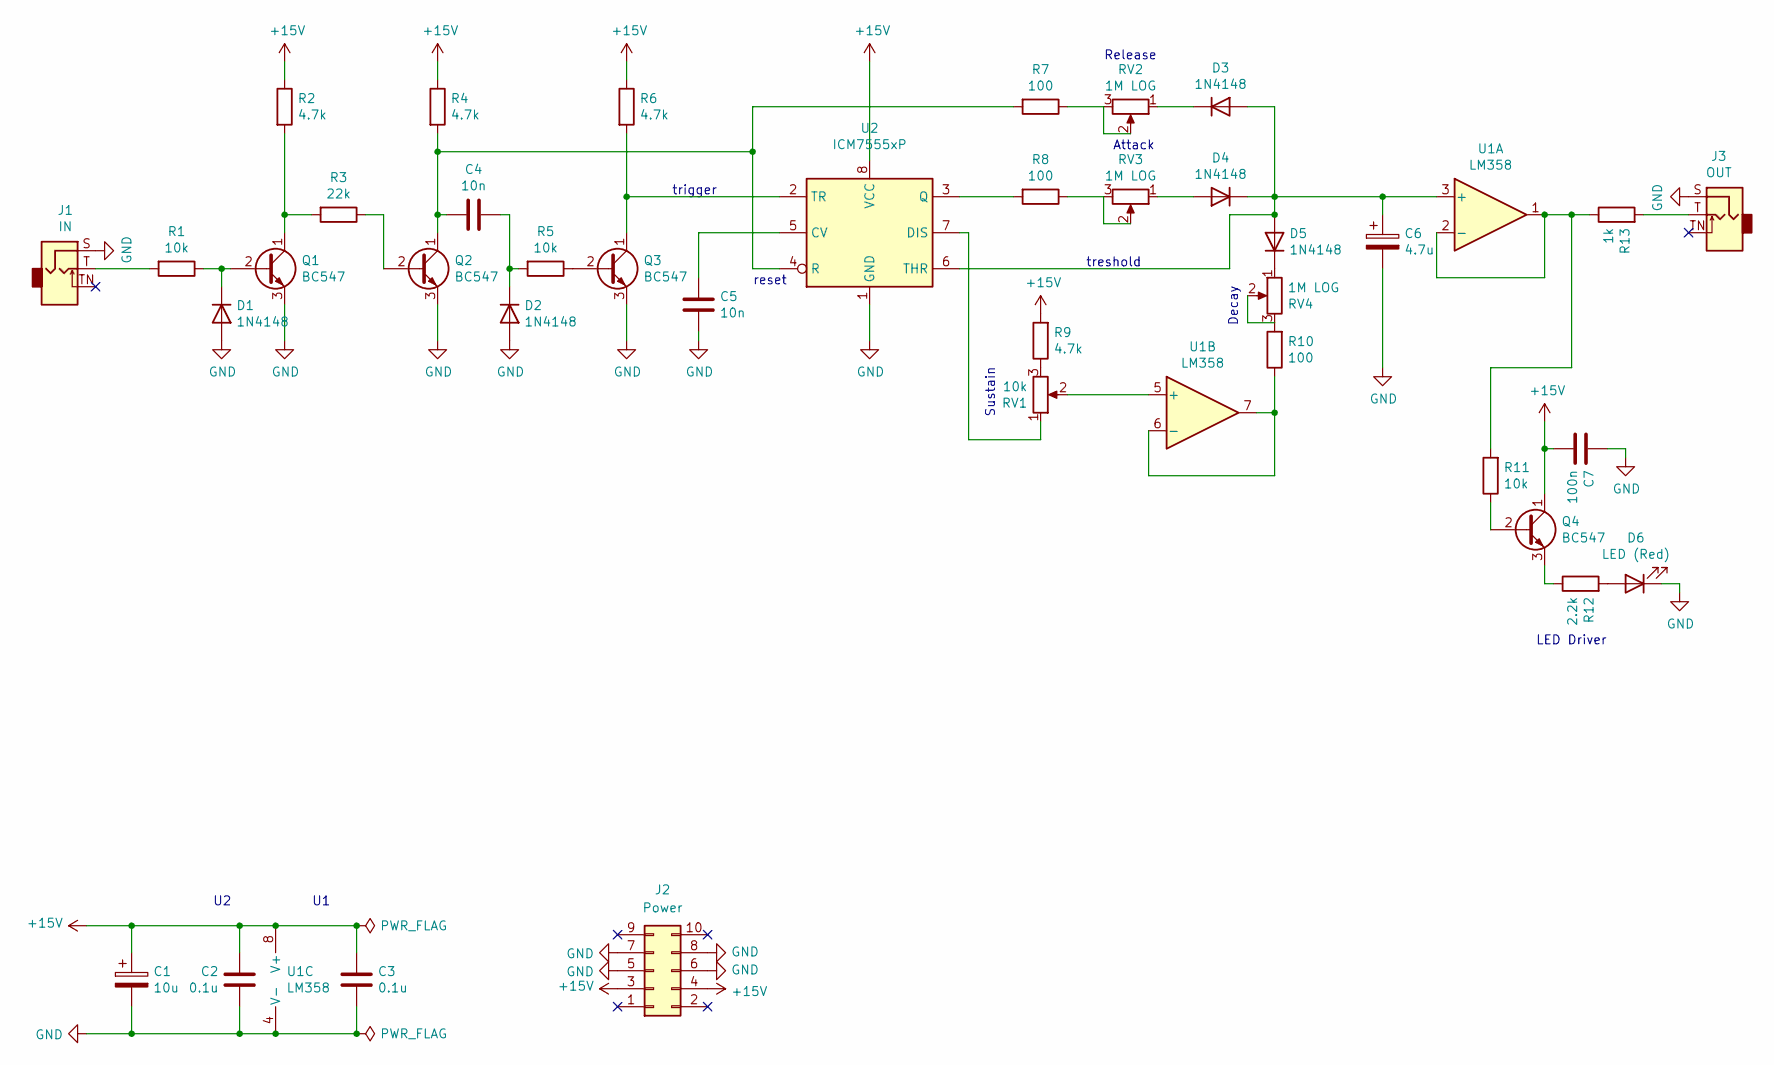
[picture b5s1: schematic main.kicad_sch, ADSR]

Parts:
C1: 10u; CP_Radial_D5.0mm_P2.50mm
C2, C3: 0.1u; C_Disc_D3.4mm_W2.1mm_P2.50mm
C4, C5: 10n; C_Rect_L4.0mm_W2.5mm_P2.50mm
C6: 4.7u; CP_Radial_D5.0mm_P2.50mm
C7: 100n; C_Rect_L4.0mm_W2.5mm_P2.50mm
D1, D2, D3, D4, D5: 1N4148; D_DO-35_SOD27_P7.62mm_Horizontal
D6: LED (Red); LED_D5.0mm
J1: IN; Jack_3.5mm_WQP-PJ398SM_Vertical
J2: Power; IDC-Header_2x05_P2.54mm_Vertical
J3: OUT; Jack_3.5mm_WQP-PJ398SM_Vertical
Q1, Q2, Q3, Q4: BC547; TO-92_Inline_Wide
R1, R5, R11: 10k; R_Axial_DIN0207_L6.3mm_D2.5mm_P10.16mm_Horizontal
R2, R4, R6, R9: 4.7k; R_Axial_DIN0207_L6.3mm_D2.5mm_P10.16mm_Horizontal
R3: 22k; R_Axial_DIN0207_L6.3mm_D2.5mm_P2.54mm_Vertical
R7, R8, R10: 100; R_Axial_DIN0207_L6.3mm_D2.5mm_P10.16mm_Horizontal
R12: 2.2k; R_Axial_DIN0207_L6.3mm_D2.5mm_P10.16mm_Horizontal
R13: 1k; R_Axial_DIN0207_L6.3mm_D2.5mm_P10.16mm_Horizontal
RV1: 10k; Potentiometer_Alpha_RD901F-40-00D_Single_Vertical
RV2, RV3, RV4: 1M LOG; Potentiometer_Alpha_RD901F-40-00D_Single_Vertical
U1: LM358; DIP-8_W7.62mm_Socket
U2: ICM7555xP; DIP-8_W7.62mm

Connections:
+15V: C1.1, C2.2, C3.1, C7.1, J2.3, J2.4, Q4.1 (C), R2.1, R4.1, R6.1, R9.2, U1.8 (V+), U2.8 (VCC)
GND: C1.2, C2.1, C3.2, C5.1, C6.2, C7.2, D1.2 (A), D2.2 (A), D6.1 (K), J1.S, J2.5, J2.6, J2.7, J2.8, J3.S, Q1.3 (E), Q2.3 (E), Q3.3 (E), U1.4 (V-), U2.1 (GND)
unnamed: D1.1 (K), Q1.2 (B), R1.1
unnamed: C4.1, D2.1 (K), R5.2
unnamed: C6.1, D3.2 (A), D4.1 (K), D5.2 (A), U1.3 (+), U2.6 (THR)
unnamed: D3.1 (K), RV2.1
unnamed: D4.2 (A), RV3.1
unnamed: D5.1 (K), RV4.1
unnamed: D6.2 (A), R12.2
unnamed: J1.T, R1.2
unnamed: J3.T, R13.2
unnamed: Q1.1 (C), R2.2, R3.2
unnamed: Q2.2 (B), R3.1
unnamed: C4.2, Q2.1 (C), R4.2, R7.2, U2.4 (R)
unnamed: Q3.2 (B), R5.1
unnamed: Q3.1 (C), R6.2, U2.2 (TR)
unnamed: Q4.2 (B), R11.1
unnamed: Q4.3 (E), R12.1
unnamed: R7.1, RV2.2, RV2.3
unnamed: R8.1, RV3.2, RV3.3
unnamed: R9.1, RV1.3
unnamed: R10.2, RV4.2, RV4.3
unnamed: R11.2, R13.1, U1.1, U1.2 (-)
unnamed: RV1.2, U1.5 (+)
unnamed: R10.1, U1.6 (-), U1.7
unnamed: C5.2, U2.5 (CV)
unnamed: RV1.1, U2.7 (DIS)
unnamed: R8.2, U2.3 (Q)

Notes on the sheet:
Release
LED Driver
reset
Sustain
Decay
Attack
trigger
treshold

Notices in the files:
src/4046/main/main.kicad_pcb:
License CC BY 4.0 - Attribution 4.0 International
